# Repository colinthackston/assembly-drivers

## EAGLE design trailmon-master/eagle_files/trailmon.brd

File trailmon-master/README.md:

# trailmon
Hardware targeted at the trail counter project

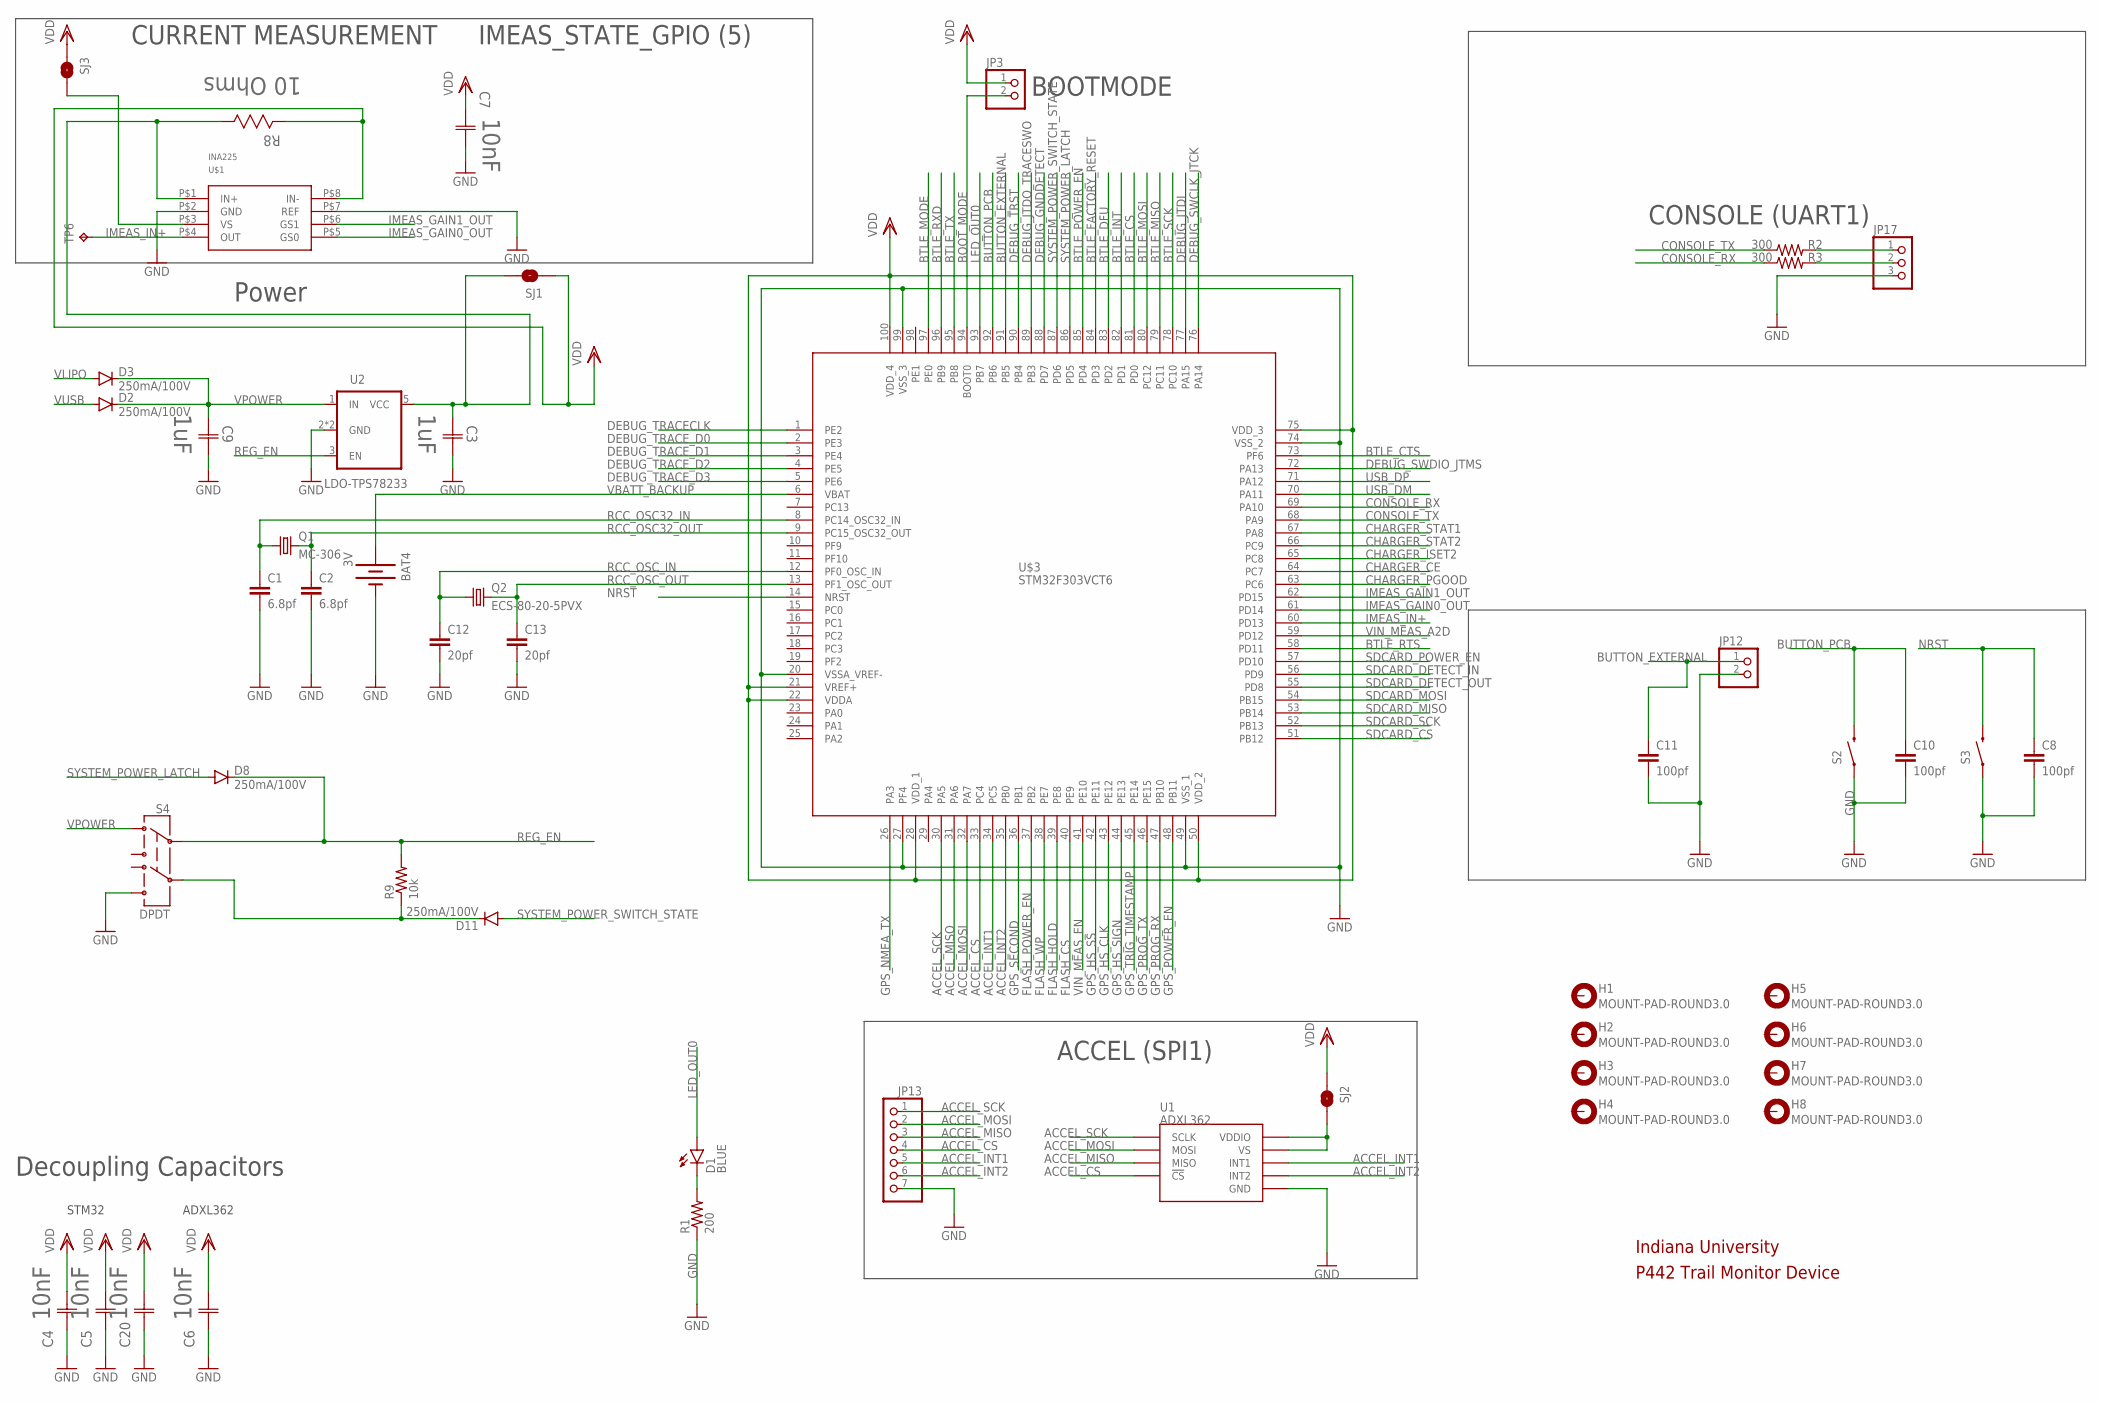
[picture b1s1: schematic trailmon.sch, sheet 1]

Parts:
BAT4: 3V; BATTCON_12MM
C1, C2: 6.8pf; 0603-CAP
C3, C9: 1uF; CAPC2013X110N
C4, C5, C6, C7, C20: 10nF; CAPC2013X88N
C8, C10, C11: 100pf; 0805
C12, C13: 20pf; 0603-CAP
D1: BLUE; LED-0603
D2, D3, D8, D11: 250mA/100V; SOD-323
H1, H2, H3, H4, H5, H6, H7, H8: MOUNT-PAD-ROUND3.0; 3,0-PAD
JP3, JP12: PINHD-1X2; 1X02
JP13: PINHD-1X7; 1X07
JP17: PINHD-1X3; 1X03
Q1: MC-306
Q2: ECS-80-20-5PVX; CSM-7X-DU
R1: 200; 0603-RES
R2, R3: 300; 0805
R8: 10 Ohms; RESC1608X60N
R9: 10k; 0603-RES
S2, S3: SWITCH-MOMENTARY-2SMD; TACTILE-SWITCH-SMD
S4: DPDT; AYZ0202
SJ1, SJ2, SJ3: JUMPER-PAD-2-NOYES_SILK; PAD-JUMPER-2-NO_YES_SILK
TP6: TPB1,27; B1,27
U1: ADXL362
U2: LDO-TPS78233; SOT23-5
U$1: INA225; MSOP-8
U$3: STM32F303VCT6; TQFP100

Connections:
ACCEL_CS: JP13.4, U1.P$8 (!CS), U$3.33 (PC4)
ACCEL_INT1: JP13.5, U1.P$11 (INT1), U$3.34 (PC5)
ACCEL_INT2: JP13.6, U1.P$9 (INT2), U$3.35 (PB0)
ACCEL_MISO: JP13.3, U1.P$7 (MISO), U$3.31 (PA6)
ACCEL_MOSI: JP13.2, U1.P$6 (MOSI), U$3.32 (PA7)
ACCEL_SCK: JP13.1, U1.P$4 (SCLK), U$3.30 (PA5)
BOOT_MODE: JP3.2, U$3.94 (BOOT0)
BTLE_CS: U$3.81 (PD0); also elsewhere on the board
BTLE_CTS: U$3.73 (PF6); also elsewhere on the board
BTLE_DFU: U$3.83 (PD2); also elsewhere on the board
BTLE_FACTORY_RESET: U$3.84 (PD3); also elsewhere on the board
BTLE_INT: U$3.82 (PD1); also elsewhere on the board
BTLE_MISO: U$3.79 (PC11); also elsewhere on the board
BTLE_MODE: U$3.97 (PE0); also elsewhere on the board
BTLE_MOSI: U$3.80 (PC12); also elsewhere on the board
BTLE_POWER_EN: U$3.85 (PD4); also elsewhere on the board
BTLE_RTS: U$3.58 (PD11); also elsewhere on the board
BTLE_RXD: U$3.96 (PB9); also elsewhere on the board
BTLE_SCK: U$3.78 (PC10); also elsewhere on the board
BTLE_TX: U$3.95 (PB8); also elsewhere on the board
BUTTON_EXTERNAL: C11.1, JP12.1, U$3.91 (PB5)
BUTTON_PCB: C10.1, S2.3 (2), U$3.92 (PB6)
CHARGER_CE: U$3.64 (PC7); also elsewhere on the board
CHARGER_ISET2: U$3.65 (PC8); also elsewhere on the board
CHARGER_PGOOD: U$3.63 (PC6); also elsewhere on the board
CHARGER_STAT1: U$3.67 (PA8); also elsewhere on the board
CHARGER_STAT2: U$3.66 (PC9); also elsewhere on the board
CONSOLE_RX: R3.1, U$3.69 (PA10)
CONSOLE_TX: R2.1, U$3.68 (PA9)
DEBUG_GNDDETECT: U$3.88 (PD7)
DEBUG_JTDI: U$3.77 (PA15); also elsewhere on the board
DEBUG_JTDO_TRACESWO: U$3.89 (PB3); also elsewhere on the board
DEBUG_SWCLK_JTCK: U$3.76 (PA14); also elsewhere on the board
DEBUG_SWDIO_JTMS: U$3.72 (PA13); also elsewhere on the board
DEBUG_TRACECLK: U$3.1 (PE2); also elsewhere on the board
DEBUG_TRACE_D0: U$3.2 (PE3); also elsewhere on the board
DEBUG_TRACE_D1: U$3.3 (PE4); also elsewhere on the board
DEBUG_TRACE_D2: U$3.4 (PE5); also elsewhere on the board
DEBUG_TRACE_D3: U$3.5 (PE6); also elsewhere on the board
DEBUG_TRST: U$3.90 (PB4); also elsewhere on the board
FLASH_CS: U$3.40 (PE9); also elsewhere on the board
FLASH_HOLD: U$3.39 (PE8); also elsewhere on the board
FLASH_POWER_EN: U$3.37 (PB2); also elsewhere on the board
FLASH_WP: U$3.38 (PE7); also elsewhere on the board
GND: BAT4.GND (-), C1.2, C2.2, C3.2 (C2), C4.1 (C1), C5.1 (C1), C6.1 (C1), C7.2 (C2), C8.2, C9.2 (C2), C10.2, C11.2, C12.2, C13.2, C20.1 (C1), JP12.2, JP13.7, JP17.3, R1.1, S2.1, S3.1, S4.6, U1.P$12 (GND), U1.P$13 (GND), U1.P$16 (GND), U2.2 (GND), U2.4 (GND), U$1.P$2 (GND), U$1.P$7 (REF), U$3.20 (VSSA_VREF-), U$3.27 (PF4), U$3.49 (VSS_1), U$3.74 (VSS_2), U$3.99 (VSS_3); also elsewhere on the board
GPS_HS_CLK: U$3.43 (PE12); also elsewhere on the board
GPS_HS_SIGN: U$3.44 (PE13); also elsewhere on the board
GPS_HS_SS: U$3.42 (PE11); also elsewhere on the board
GPS_NMEA_TX: U$3.26 (PA3); also elsewhere on the board
GPS_POWER_EN: U$3.48 (PB11); also elsewhere on the board
GPS_PROG_RX: U$3.47 (PB10); also elsewhere on the board
GPS_PROG_TX: U$3.46 (PE15); also elsewhere on the board
GPS_SECOND: U$3.36 (PB1); also elsewhere on the board
GPS_TRIG_TIMESTAMP: U$3.45 (PE14); also elsewhere on the board
IMEAS_GAIN0_OUT: U$1.P$5 (GS0), U$3.61 (PD14)
IMEAS_GAIN1_OUT: U$1.P$6 (GS1), U$3.62 (PD15)
IMEAS_IN+: TP6.TP, U$1.P$4 (OUT), U$3.60 (PD13)
LED_OUT0: D1.A, U$3.93 (PB7)
unnamed: D1.C, R1.2
unnamed: D11.C, R9.1, S4.5
unnamed: JP17.1, R2.2
unnamed: JP17.2, R3.2
unnamed: SJ2.2, U1.P$1 (VDDIO), U1.P$14 (VS)
unnamed: SJ3.2, U$1.P$3 (VS)
NRST: C8.1, S3.3 (2), U$3.14 (NRST); also elsewhere on the board
RCC_OSC32_IN: C1.1, Q1.1, U$3.8 (PC14_OSC32_IN)
RCC_OSC32_OUT: C2.1, Q1.4 (2), U$3.9 (PC15_OSC32_OUT)
RCC_OSC_IN: C12.1, Q2.1, U$3.12 (PF0_OSC_IN)
RCC_OSC_OUT: C13.1, Q2.2, U$3.13 (PF1_OSC_OUT)
REG_EN: D8.C, R9.2, S4.2, U2.3 (EN)
SDCARD_CS: U$3.51 (PB12); also elsewhere on the board
SDCARD_DETECT_IN: U$3.56 (PD9); also elsewhere on the board
SDCARD_DETECT_OUT: U$3.55 (PD8); also elsewhere on the board
SDCARD_MISO: U$3.53 (PB14); also elsewhere on the board
SDCARD_MOSI: U$3.54 (PB15); also elsewhere on the board
SDCARD_POWER_EN: U$3.57 (PD10); also elsewhere on the board
SDCARD_SCK: U$3.52 (PB13); also elsewhere on the board
SYSTEM_POWER_LATCH: D8.A, U$3.86 (PD5)
SYSTEM_POWER_SWITCH_STATE: D11.A, U$3.87 (PD6)
USB_DM: U$3.70 (PA11); also elsewhere on the board
USB_DP: U$3.71 (PA12); also elsewhere on the board
VBATT_BACKUP: BAT4.PWR@1 (+), U$3.6 (VBAT)
VCC: C3.1 (C1), R8.1, SJ1.2, U2.5 (VCC), U$1.P$1 (IN+)
VDD: C4.2 (C2), C5.2 (C2), C6.2 (C2), C7.1 (C1), C20.2 (C2), JP3.1, R8.2, SJ1.1, SJ2.1, SJ3.1, U$1.P$8 (IN-), U$3.21 (VREF+), U$3.22 (VDDA), U$3.28 (VDD_1), U$3.50 (VDD_2), U$3.75 (VDD_3), U$3.100 (VDD_4); also elsewhere on the board
VIN_MEAS_A2D: U$3.59 (PD12); also elsewhere on the board
VIN_MEAS_EN: U$3.41 (PE10); also elsewhere on the board
VLIPO: D3.A; also elsewhere on the board
VPOWER: C9.1 (C1), D2.C, D3.C, S4.1, U2.1 (IN)
VUSB: D2.A; also elsewhere on the board

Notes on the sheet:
Indiana University
Decoupling Capacitors
STM32
ADXL362
Power
ACCEL (SPI1)
BOOTMODE
CONSOLE (UART1)
CURRENT MEASUREMENT
P442 Trail Monitor Device
IMEAS_STATE_GPIO (5)

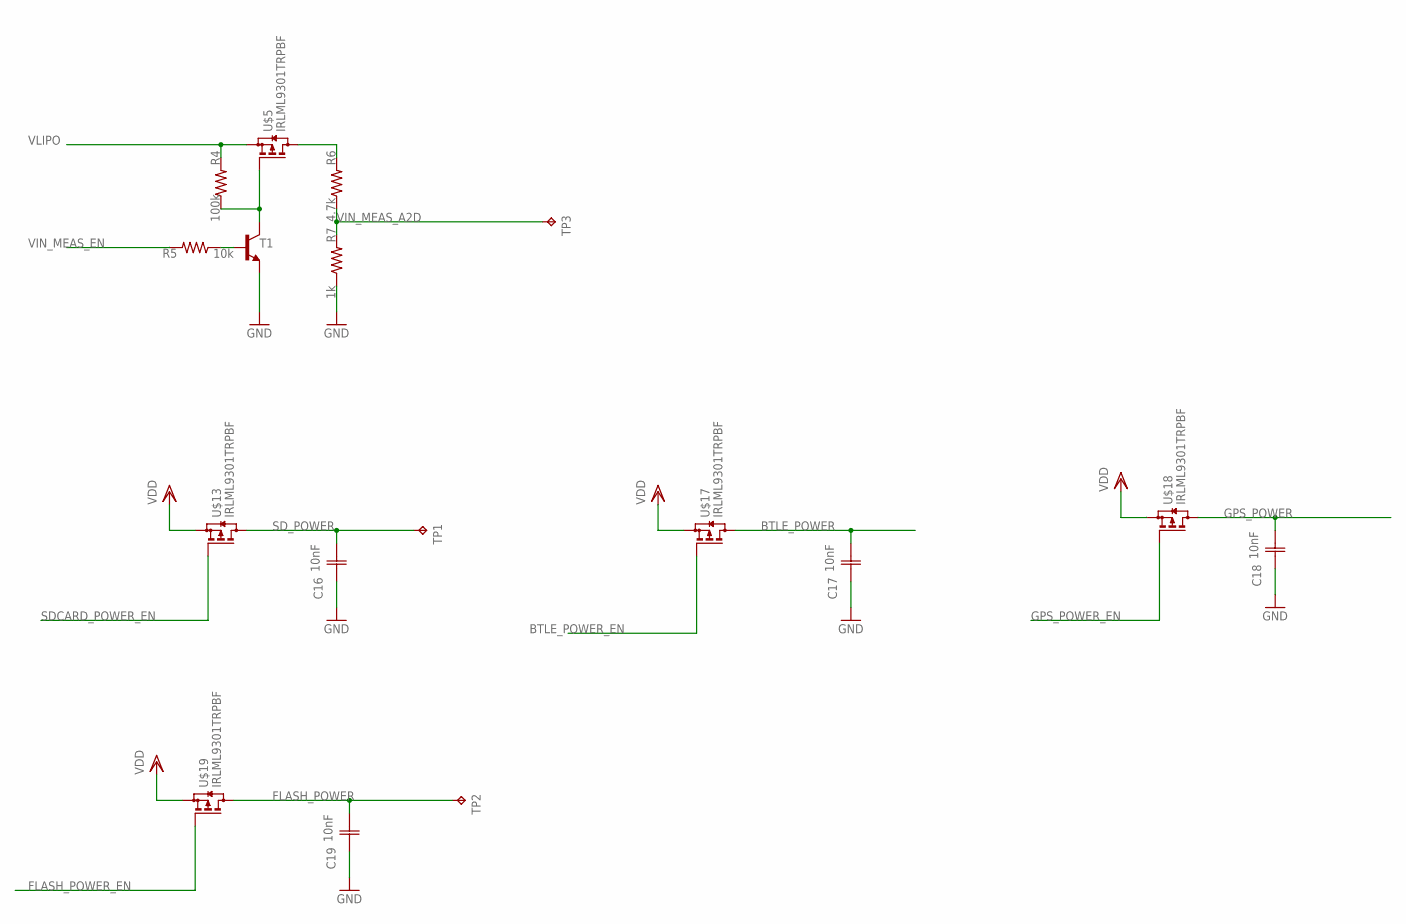
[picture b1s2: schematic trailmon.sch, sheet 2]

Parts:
C16, C17, C18, C19: 10nF; CAPC2013X88N
R4: 100k; 0805
R5: 10k; 0805
R6: 4.7k; 0805
R7: 1k; 0805
T1: BC847; SOT23
TP1, TP2, TP3: TPB1,27; B1,27
U$5, U$13, U$17, U$18, U$19: IRLML9301TRPBF; SOT23

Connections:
BTLE_POWER: C17.2 (C2), U$17.3 (D); also elsewhere on the board
BTLE_POWER_EN: U$17.1 (G); also elsewhere on the board
FLASH_POWER: C19.2 (C2), TP2.TP, U$19.3 (D); also elsewhere on the board
FLASH_POWER_EN: U$19.1 (G); also elsewhere on the board
GND: C16.1 (C1), C17.1 (C1), C18.1 (C1), C19.1 (C1), R7.1, T1.2 (E); also elsewhere on the board
GPS_POWER: C18.2 (C2), U$18.3 (D); also elsewhere on the board
GPS_POWER_EN: U$18.1 (G); also elsewhere on the board
unnamed: R5.1, T1.1 (B)
unnamed: R4.1, T1.3 (C), U$5.1 (G)
unnamed: R6.2, U$5.3 (D)
SDCARD_POWER_EN: U$13.1 (G); also elsewhere on the board
SD_POWER: C16.2 (C2), TP1.TP, U$13.3 (D); also elsewhere on the board
VDD: U$13.2 (S), U$17.2 (S), U$18.2 (S), U$19.2 (S); also elsewhere on the board
VIN_MEAS_A2D: R6.1, R7.2, TP3.TP; also elsewhere on the board
VIN_MEAS_EN: R5.2; also elsewhere on the board
VLIPO: R4.2, U$5.2 (S); also elsewhere on the board

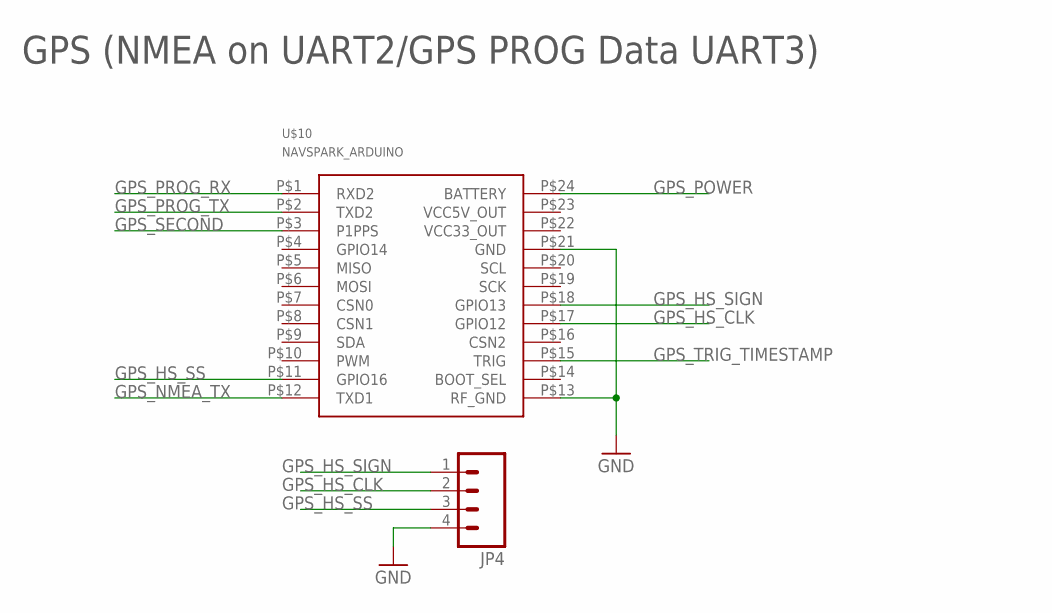
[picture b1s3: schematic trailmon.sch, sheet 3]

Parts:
JP4: M04PTH; 1X04
U$10: NAVSPARK_ARDUINO

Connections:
GND: JP4.4, U$10.P$13 (RF_GND), U$10.P$21 (GND); also elsewhere on the board
GPS_HS_CLK: JP4.2, U$10.P$17 (GPIO12); also elsewhere on the board
GPS_HS_SIGN: JP4.1, U$10.P$18 (GPIO13); also elsewhere on the board
GPS_HS_SS: JP4.3, U$10.P$11 (GPIO16); also elsewhere on the board
GPS_NMEA_TX: U$10.P$12 (TXD1); also elsewhere on the board
GPS_POWER: U$10.P$24 (BATTERY); also elsewhere on the board
GPS_PROG_RX: U$10.P$1 (RXD2); also elsewhere on the board
GPS_PROG_TX: U$10.P$2 (TXD2); also elsewhere on the board
GPS_SECOND: U$10.P$3 (P1PPS); also elsewhere on the board
GPS_TRIG_TIMESTAMP: U$10.P$15 (TRIG); also elsewhere on the board

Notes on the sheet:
GPS (NMEA on UART2/GPS PROG Data UART3)

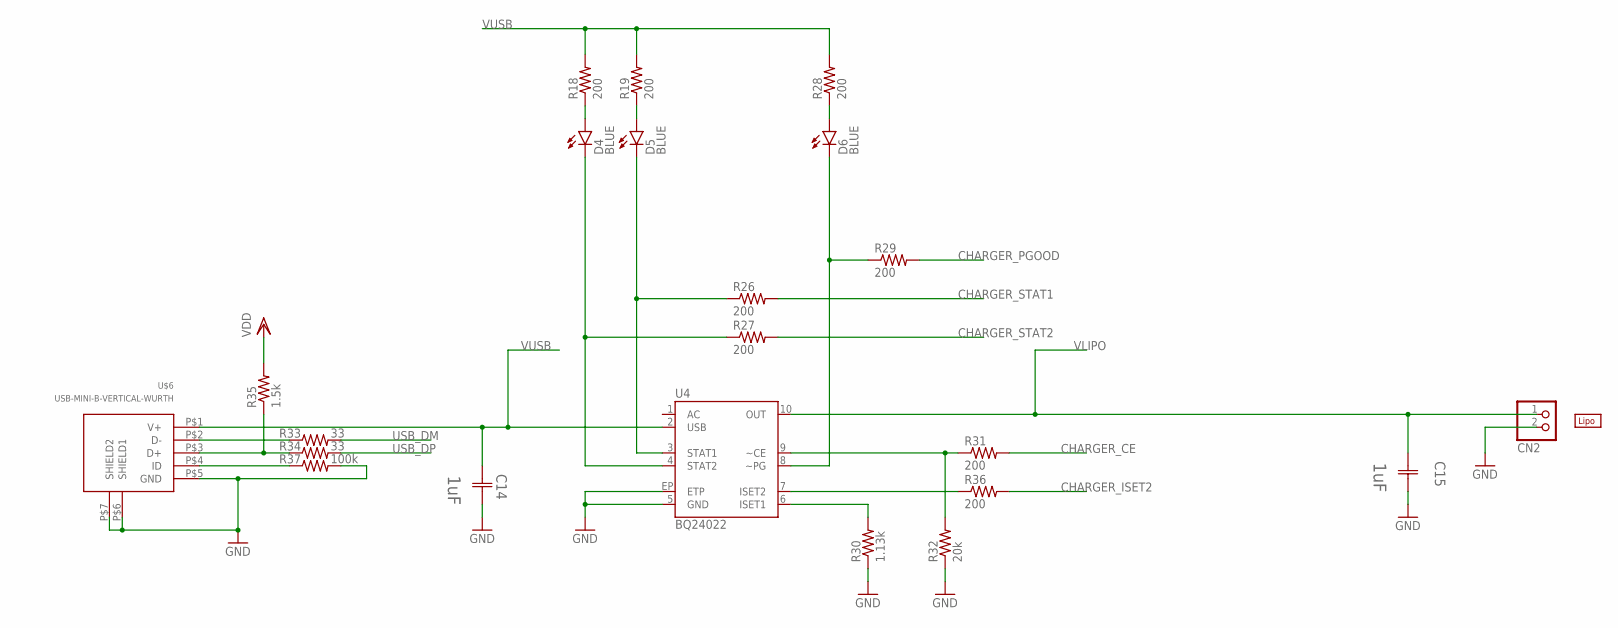
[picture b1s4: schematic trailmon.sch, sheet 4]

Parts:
C14, C15: 1uF; CAPC2013X110N
CN2: JST_2PIN-THM; JST-PH-2-THM
D4, D5, D6: BLUE; LED-0603
R18, R19, R26, R27, R28, R29, R31, R36: 200; 0603-RES
R30: 1.13k; 0603-RES
R32: 20k; 0603-RES
R33, R34: 33; 0603-RES
R35: 1.5k; 0603-RES
R37: 100k; 0603-RES
U4: BQ24022; DRC-10
U$6: USB-MINI-B-VERTICAL-WURTH; MINI-B-VERTICAL-WURTH
U$16: LIPO-OUTLINE1100; LIPO-1100

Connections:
CHARGER_CE: R31.2; also elsewhere on the board
CHARGER_ISET2: R36.2; also elsewhere on the board
CHARGER_PGOOD: R29.2; also elsewhere on the board
CHARGER_STAT1: R26.2; also elsewhere on the board
CHARGER_STAT2: R27.2; also elsewhere on the board
GND: C14.2 (C2), C15.2 (C2), CN2.2 (1), R30.1, R32.1, R37.2, U4.5 (GND), U4.EP (ETP), U$6.P$5 (GND), U$6.P$6 (SHIELD1), U$6.P$7 (SHIELD2); also elsewhere on the board
unnamed: D4.C, R27.1, U4.4 (STAT2)
unnamed: R33.1, U$6.P$2 (D-)
unnamed: D4.A, R18.1
unnamed: D5.C, R26.1, U4.3 (STAT1)
unnamed: D5.A, R19.1
unnamed: D6.A, R28.1
unnamed: D6.C, R29.1, U4.8 (~PG)
unnamed: R30.2, U4.6 (ISET1)
unnamed: R31.1, R32.2, U4.9 (~CE)
unnamed: R34.1, R35.1, U$6.P$3 (D+)
unnamed: R36.1, U4.7 (ISET2)
unnamed: R37.1, U$6.P$4 (ID)
USB_DM: R33.2; also elsewhere on the board
USB_DP: R34.2; also elsewhere on the board
VDD: R35.2; also elsewhere on the board
VLIPO: C15.1 (C1), CN2.1 (2), U4.10 (OUT); also elsewhere on the board
VUSB: C14.1 (C1), R18.2, R19.2, R28.2, U4.2 (USB), U$6.P$1 (V+); also elsewhere on the board

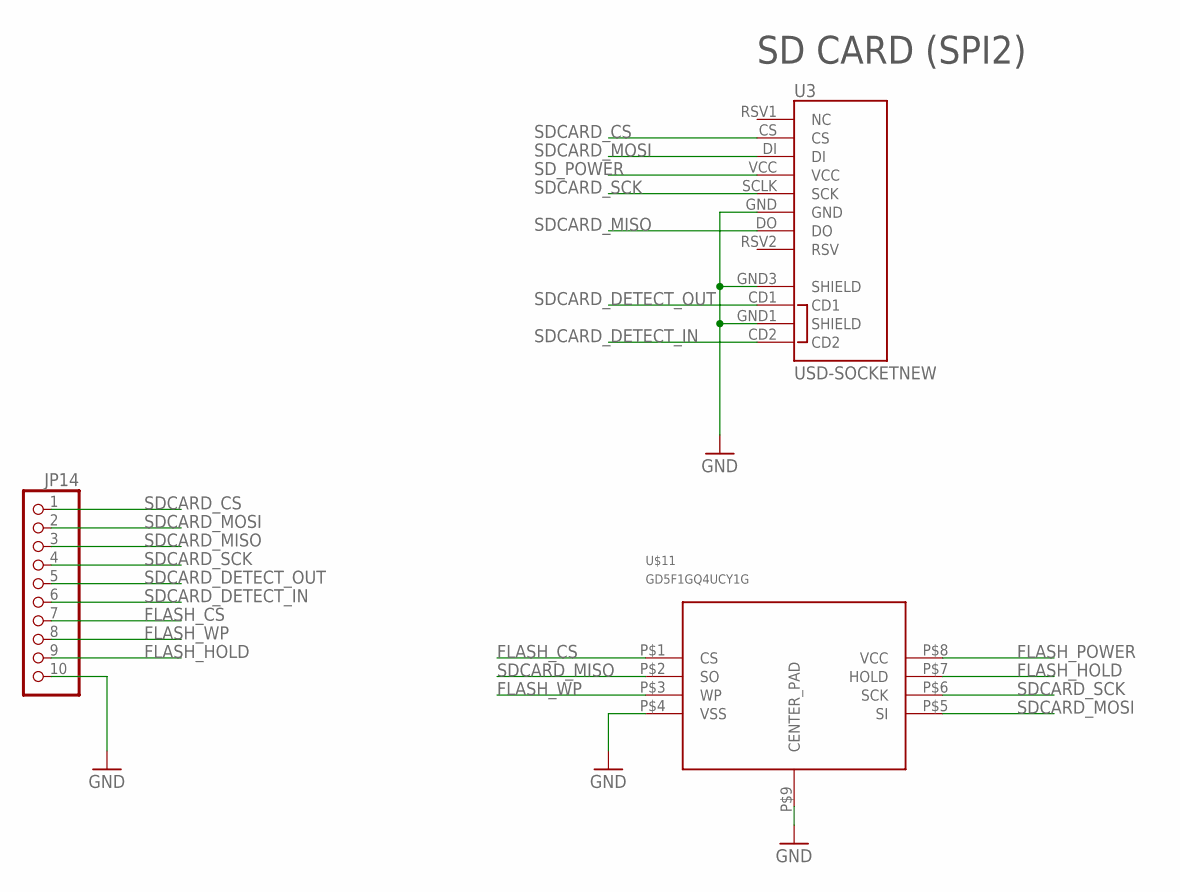
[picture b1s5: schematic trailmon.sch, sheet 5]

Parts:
JP14: PINHD-1X10; 1X10
U3: USD-SOCKETNEW; MICRO-SD-SOCKET-PP
U$11: GD5F1GQ4UCY1G; WSON-8

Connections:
FLASH_CS: JP14.7, U$11.P$1 (CS); also elsewhere on the board
FLASH_HOLD: JP14.9, U$11.P$7 (HOLD); also elsewhere on the board
FLASH_POWER: U$11.P$8 (VCC); also elsewhere on the board
FLASH_WP: JP14.8, U$11.P$3 (WP); also elsewhere on the board
GND: JP14.10, U3.GND, U3.GND1 (SHIELD), U3.GND3 (SHIELD), U$11.P$4 (VSS), U$11.P$9 (CENTER_PAD); also elsewhere on the board
SDCARD_CS: JP14.1, U3.CS; also elsewhere on the board
SDCARD_DETECT_IN: JP14.6, U3.CD2; also elsewhere on the board
SDCARD_DETECT_OUT: JP14.5, U3.CD1; also elsewhere on the board
SDCARD_MISO: JP14.3, U3.DO, U$11.P$2 (SO); also elsewhere on the board
SDCARD_MOSI: JP14.2, U3.DI, U$11.P$5 (SI); also elsewhere on the board
SDCARD_SCK: JP14.4, U3.SCLK (SCK), U$11.P$6 (SCK); also elsewhere on the board
SD_POWER: U3.VCC; also elsewhere on the board

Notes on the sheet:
SD CARD (SPI2)

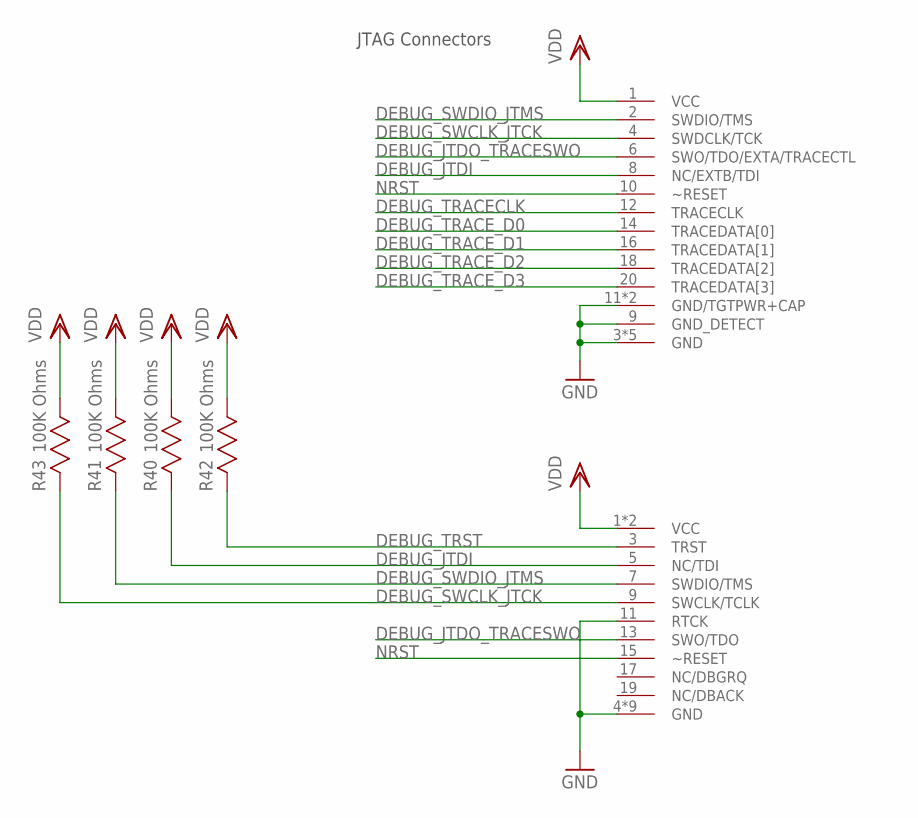
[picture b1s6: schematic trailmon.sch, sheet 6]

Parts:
R40, R41, R42, R43: 100K Ohms; RESC1005X40N
U$2: 2X10_0.05"_CORTEX_DEBUG_WITH_ETMSMD_UNSHROUDED; 2X10_0.05"_SMD_NS
U$12: TRADITIONALJTAG/SWDTH_SHROUDED; 2X10_0.1"_TH_SH

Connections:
DEBUG_JTDI: R40.2, U$2.8 (NC/EXTB/TDI), U$12.5 (NC/TDI); also elsewhere on the board
DEBUG_JTDO_TRACESWO: U$2.6 (SWO/TDO/EXTA/TRACECTL), U$12.13 (SWO/TDO); also elsewhere on the board
DEBUG_SWCLK_JTCK: R43.2, U$2.4 (SWDCLK/TCK), U$12.9 (SWCLK/TCLK); also elsewhere on the board
DEBUG_SWDIO_JTMS: R41.2, U$2.2 (SWDIO/TMS), U$12.7 (SWDIO/TMS); also elsewhere on the board
DEBUG_TRACECLK: U$2.12 (TRACECLK); also elsewhere on the board
DEBUG_TRACE_D0: U$2.14 (TRACEDATA[0]); also elsewhere on the board
DEBUG_TRACE_D1: U$2.16 (TRACEDATA[1]); also elsewhere on the board
DEBUG_TRACE_D2: U$2.18 (TRACEDATA[2]); also elsewhere on the board
DEBUG_TRACE_D3: U$2.20 (TRACEDATA[3]); also elsewhere on the board
DEBUG_TRST: R42.2, U$12.3 (TRST); also elsewhere on the board
GND: U$2.3 (GND), U$2.5 (GND), U$2.9 (GND_DETECT), U$2.11 (GND/TGTPWR+CAP), U$2.13 (GND/TGTPWR+CAP), U$2.15 (GND), U$2.17 (GND), U$2.19 (GND), U$12.4 (GND), U$12.6 (GND), U$12.8 (GND), U$12.10 (GND), U$12.11 (RTCK), U$12.12 (GND), U$12.14 (GND), U$12.16 (GND), U$12.18 (GND), U$12.20 (GND); also elsewhere on the board
NRST: U$2.10 (~RESET), U$12.15 (~RESET); also elsewhere on the board
VDD: R40.1, R41.1, R42.1, R43.1, U$2.1 (VCC), U$12.1 (VCC), U$12.2 (VCC); also elsewhere on the board

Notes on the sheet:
JTAG Connectors

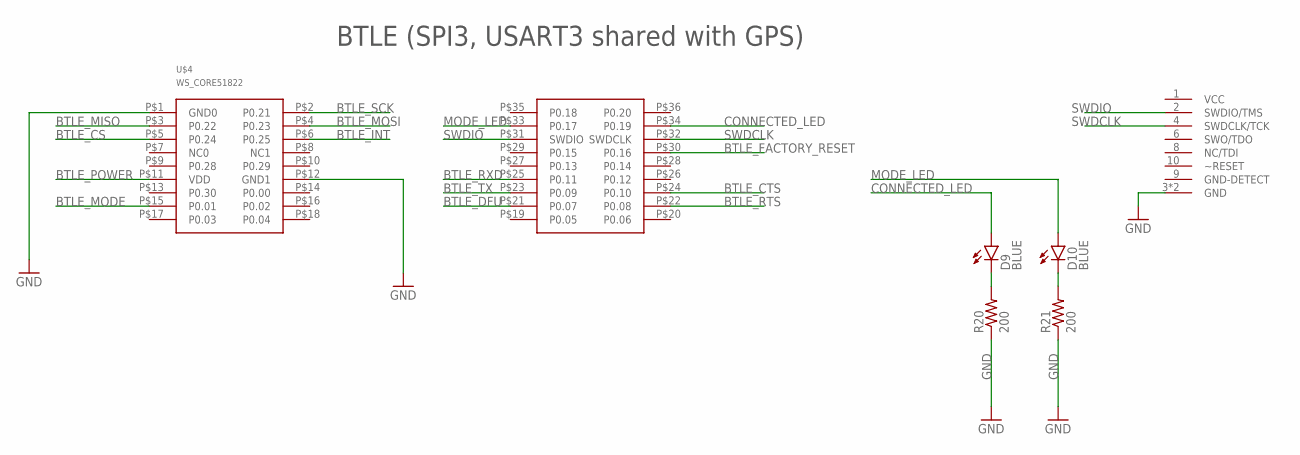
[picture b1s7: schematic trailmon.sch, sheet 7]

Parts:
D9, D10: BLUE; LED-0603
R20, R21: 200; 0603-RES
U$4: WS_CORE51822
U$15: 2X5_0.05"_CORTEX_DEBUGTH_NOKEY_UNSHROUDED; 2X5_0.05"_TH_NS

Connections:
BTLE_CS: U$4.P$5 (P0.24); also elsewhere on the board
BTLE_CTS: U$4.P$24 (P0.10); also elsewhere on the board
BTLE_DFU: U$4.P$21 (P0.07); also elsewhere on the board
BTLE_FACTORY_RESET: U$4.P$30 (P0.16); also elsewhere on the board
BTLE_INT: U$4.P$6 (P0.25); also elsewhere on the board
BTLE_MISO: U$4.P$3 (P0.22); also elsewhere on the board
BTLE_MODE: U$4.P$15 (P0.01); also elsewhere on the board
BTLE_MOSI: U$4.P$4 (P0.23); also elsewhere on the board
BTLE_POWER: U$4.P$11 (VDD); also elsewhere on the board
BTLE_RTS: U$4.P$22 (P0.08); also elsewhere on the board
BTLE_RXD: U$4.P$25 (P0.11); also elsewhere on the board
BTLE_SCK: U$4.P$2 (P0.21); also elsewhere on the board
BTLE_TX: U$4.P$23 (P0.09); also elsewhere on the board
CONNECTED_LED: D9.A, U$4.P$34 (P0.19)
GND: R20.1, R21.1, U$4.P$1 (GND0), U$4.P$12 (GND1), U$15.3 (GND), U$15.5 (GND); also elsewhere on the board
MODE_LED: D10.A, U$4.P$33 (P0.17)
unnamed: D9.C, R20.2
unnamed: D10.C, R21.2
SWDCLK: U$4.P$32 (SWDCLK), U$15.4 (SWDCLK/TCK)
SWDIO: U$4.P$31 (SWDIO), U$15.2 (SWDIO/TMS)

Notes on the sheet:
BTLE (SPI3, USART3 shared with GPS)

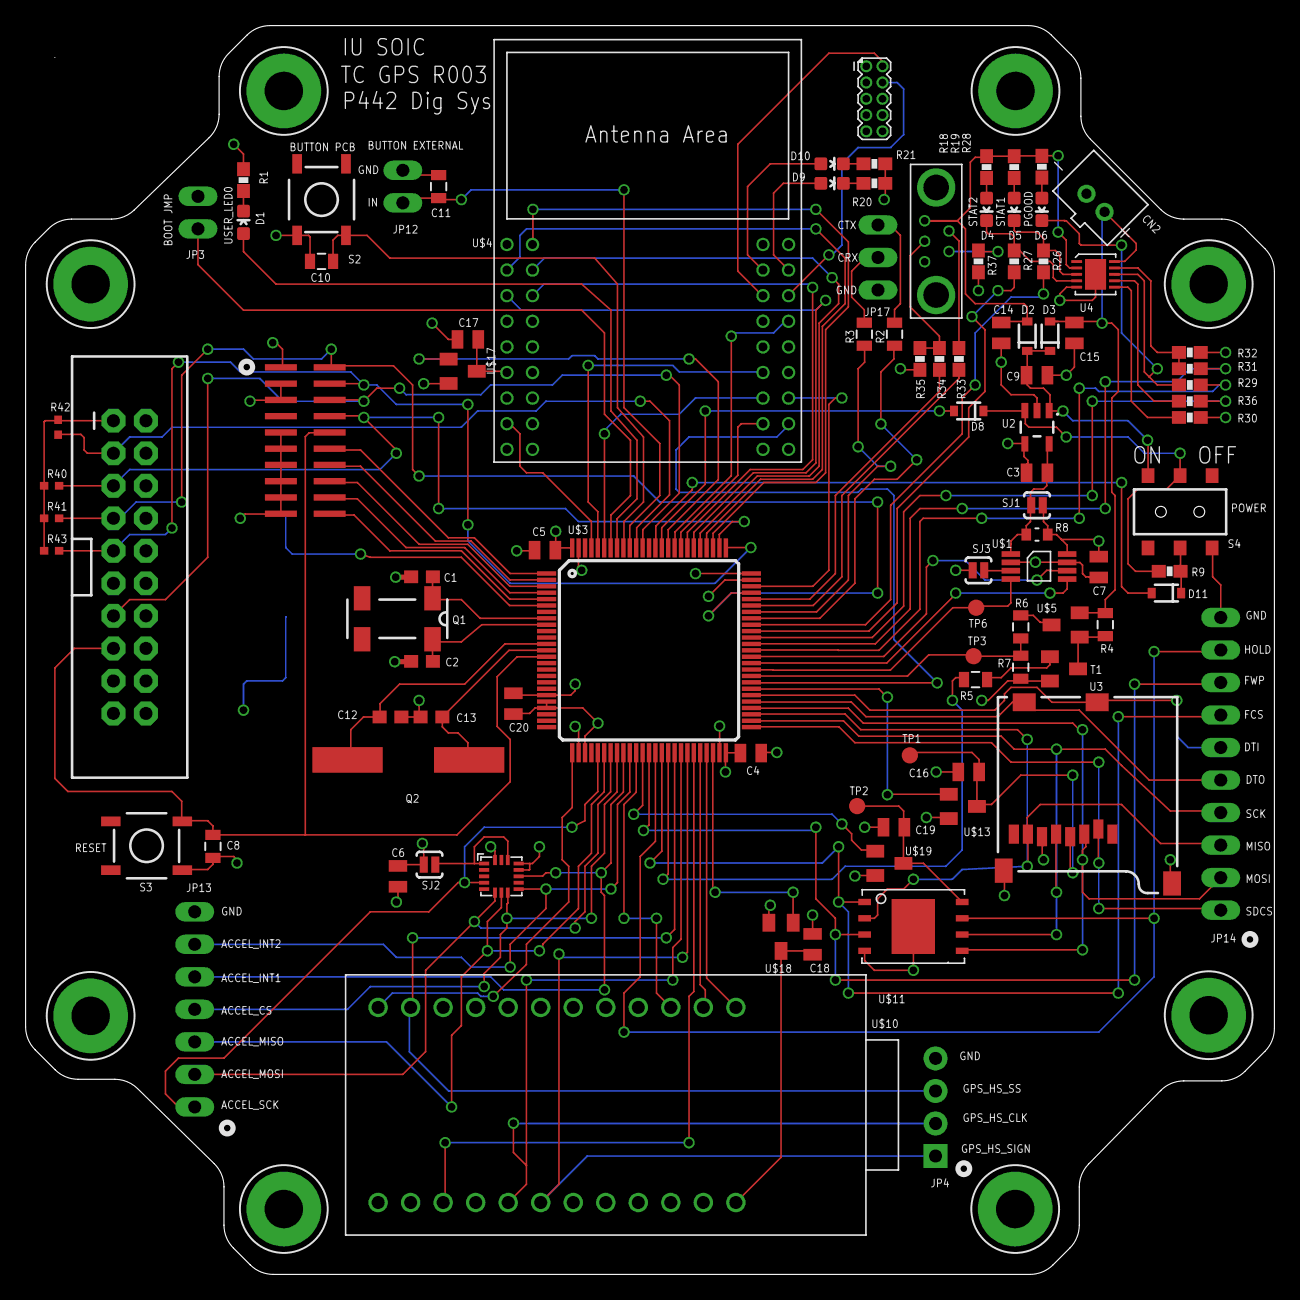
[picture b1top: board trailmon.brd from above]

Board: 4 copper layers, 97.5 x 97.5 mm, 107 parts (1 on the bottom side), 113 nets.

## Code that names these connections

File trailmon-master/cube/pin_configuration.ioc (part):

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Mcu.Name=STM32F303V(D-E)Tx
Mcu.Package=LQFP100
Mcu.UserName=STM32F303VETx
PA10.GPIOParameters=GPIO_Label
PA10.GPIO_Label=CONSOLE_RX
PA10.Mode=Asynchronous
PA10.Signal=USART1_RX
PA11.Mode=Device
PA11.Signal=USB_DM
PA12.Mode=Device
PA12.Signal=USB_DP
PA13.GPIOParameters=GPIO_Label
PA13.GPIO_Label=DEBUG_SWDIO_JTMS
PA13.Mode=Trace_Synchro_4bits_JTAG
PA13.Signal=SYS_JTMS-SWDIO
PA14.GPIOParameters=GPIO_Label
PA14.GPIO_Label=DEBUG_SWCLK_JTCK
PA14.Mode=Trace_Synchro_4bits_JTAG
PA14.Signal=SYS_JTCK-SWCLK
PA15.GPIOParameters=GPIO_Label
PA15.GPIO_Label=DEBUG_JTDI
PA15.Mode=Trace_Synchro_4bits_JTAG
PA15.Signal=SYS_JTDI
PA3.GPIOParameters=GPIO_Label
PA3.GPIO_Label=GPS_NMEA_TX
PA3.Signal=USART2_RX
PA5.GPIOParameters=GPIO_Label
PA5.GPIO_Label=ACCEL_SCK
PA5.Mode=Full_Duplex_Master
PA5.Signal=SPI1_SCK
PA6.GPIOParameters=GPIO_Label
PA6.GPIO_Label=ACCEL_MISO
PA6.Mode=Full_Duplex_Master
PA6.Signal=SPI1_MISO
PA7.GPIOParameters=GPIO_Label
PA7.GPIO_Label=ACCEL_MOSI
PA7.Mode=Full_Duplex_Master
PA7.Signal=SPI1_MOSI
PA8.GPIOParameters=GPIO_Label
PA8.GPIO_Label=CHARGER_STAT1
PA8.Signal=GPIO_Input
PA9.GPIOParameters=GPIO_Label
PA9.GPIO_Label=CONSOLE_TX
PA9.Mode=Asynchronous
PA9.Signal=USART1_TX
PB0.GPIOParameters=GPIO_Label
PB0.GPIO_Label=ACCEL_INT2
PB0.Signal=GPXTI0
PB1.GPIOParameters=GPIO_Label
PB1.GPIO_Label=GPS_SECOND
PB1.Signal=S_TIM3_CH4
PB10.GPIOParameters=GPIO_Label
PB10.GPIO_Label=GPS_PROG_RX
PB10.Mode=Asynchronous
PB10.Signal=USART3_TX
PB11.GPIOParameters=GPIO_Label
PB11.GPIO_Label=GPS_POWER_EN
PB11.Signal=GPIO_Output
PB12.GPIOParameters=GPIO_Label
PB12.GPIO_Label=SDCARD_CS
PB12.Signal=GPIO_Output
PB13.GPIOParameters=GPIO_Label
PB13.GPIO_Label=SDCARD_SCK
PB13.Mode=Full_Duplex_Master
PB13.Signal=SPI2_SCK
PB14.GPIOParameters=GPIO_Label
PB14.GPIO_Label=SDCARD_MISO
PB14.Mode=Full_Duplex_Master
PB14.Signal=SPI2_MISO
PB15.GPIOParameters=GPIO_Label
PB15.GPIO_Label=SDCARD_MOSI
PB15.Mode=Full_Duplex_Master
PB15.Signal=SPI2_MOSI
PB2.GPIOParameters=GPIO_Label
PB2.GPIO_Label=FLASH_POWER_EN
PB2.Signal=GPIO_Output
PB3.GPIOParameters=GPIO_Label
PB3.GPIO_Label=DEBUG_JTDO_TRACESWO
PB3.Mode=Trace_Synchro_4bits_JTAG
PB3.Signal=SYS_JTDO-TRACESWO
PB4.GPIOParameters=GPIO_Label
PB4.GPIO_Label=DEBUG_TRST
PB4.Signal=SYS_NJTRST
PB5.GPIOParameters=GPIO_Label
PB5.GPIO_Label=BUTTON_EXTERNAL
PB5.Signal=GPIO_Input
PB6.GPIOParameters=GPIO_Label
PB6.GPIO_Label=BUTTON_PCB
PB6.Signal=GPXTI6
PB7.GPIOParameters=GPIO_Label
PB7.GPIO_Label=LED_OUT
PB7.Signal=GPIO_Output
PB8.GPIOParameters=GPIO_Label
PB8.GPIO_Label=BTLE_TX
PB8.Signal=GPIO_Input
PB9.GPIOParameters=GPIO_Label
PB9.GPIO_Label=BTLE_RXD
PB9.Signal=GPIO_Output
PC10.GPIOParameters=GPIO_Label
PC10.GPIO_Label=BTLE_SCK
PC10.Mode=Full_Duplex_Master
PC10.Signal=SPI3_SCK
PC11.GPIOParameters=GPIO_Label
PC11.GPIO_Label=BTLE_MISO
PC11.Mode=Full_Duplex_Master
PC11.Signal=SPI3_MISO
PC12.GPIOParameters=GPIO_Label
PC12.GPIO_Label=BTLE_MOSI
PC12.Mode=Full_Duplex_Master
PC12.Signal=SPI3_MOSI
PC14-OSC32_IN.Mode=LSE-External-Oscillator
PC14-OSC32_IN.Signal=RCC_OSC32_IN
PC15-OSC32_OUT.Mode=LSE-External-Oscillator
PC15-OSC32_OUT.Signal=RCC_OSC32_OUT
PC4.GPIOParameters=GPIO_Label
PC4.GPIO_Label=ACCEL_CS
PC4.Signal=GPIO_Output
PC5.GPIOParameters=GPIO_Label
PC5.GPIO_Label=ACCEL_INT1
PC5.Signal=GPXTI5
PC6.GPIOParameters=GPIO_Label
PC6.GPIO_Label=CHARGER_PGOOD
PC6.Signal=GPIO_Input
PC7.GPIOParameters=GPIO_Label
PC7.GPIO_Label=CHARGER_CE
PC7.Signal=GPIO_Output
PC8.GPIOParameters=GPIO_Label
PC8.GPIO_Label=CHARGER_ISET2
PC8.Signal=GPIO_Output
PC9.GPIOParameters=GPIO_Label
PC9.GPIO_Label=CHARGER_STAT2
PC9.Signal=GPIO_Input
PD0.GPIOParameters=GPIO_Label
PD0.GPIO_Label=BTLE_CS
PD0.Signal=GPIO_Output
PD1.GPIOParameters=GPIO_Label
PD1.GPIO_Label=BTLE_INT
PD1.Signal=GPXTI1
PD10.GPIOParameters=GPIO_Label
PD10.GPIO_Label=SDCARD_POWER_EN
PD10.Signal=GPIO_Output
PD11.GPIOParameters=GPIO_Label
PD11.GPIO_Label=BTLE_RTS
PD11.Mode=CTS_RTS
PD11.Signal=USART3_CTS
PD12.GPIOParameters=GPIO_Label
PD12.GPIO_Label=VIN_MEAS_A2D
PD12.Signal=ADCx_IN9P
PD13.GPIOParameters=GPIO_Label
PD13.GPIO_Label=IMEAS_IN+
PD13.Signal=ADCx_IN10P
PD14.GPIOParameters=GPIO_Label
PD14.GPIO_Label=IMEAS_GAIN0_OUT
PD14.Signal=GPIO_Output
PD15.GPIOParameters=GPIO_Label
PD15.GPIO_Label=IMEAS_GAIN1_OUT
PD15.Signal=GPIO_Output
PD2.GPIOParameters=GPIO_Label
PD2.GPIO_Label=BTLE_DFU
PD2.Signal=GPIO_Output
PD3.GPIOParameters=GPIO_Label
PD3.GPIO_Label=BTLE_FACTORY_RESET
PD3.Signal=GPIO_Output
PD4.GPIOParameters=GPIO_Label
PD4.GPIO_Label=BTLE_POWER_EN
PD4.Signal=GPIO_Output
PD5.GPIOParameters=GPIO_Label
PD5.GPIO_Label=SYSTEM_POWER_LATCH
PD5.Signal=GPIO_Output
PD6.GPIOParameters=GPIO_Label
PD6.GPIO_Label=SYSTEM_POWER_SWITCH_STATE
PD6.Signal=GPIO_Output
PD7.GPIOParameters=GPIO_Label
PD7.GPIO_Label=DEBUG_GNDDETECT
PD7.Signal=GPIO_Input
PD8.GPIOParameters=GPIO_Label
PD8.GPIO_Label=SDCARD_DETECT_OUT
PD8.Signal=GPIO_Output
PD9.GPIOParameters=GPIO_Label
PD9.GPIO_Label=SDCARD_DETECT_IN
PD9.Signal=GPXTI9
PE0.GPIOParameters=GPIO_Label
PE0.GPIO_Label=BTLE_MODE
PE0.Signal=GPIO_Output
PE10.GPIOParameters=GPIO_Label
PE10.GPIO_Label=VIN_MEAS_EN
PE10.Signal=GPIO_Output
PE11.GPIOParameters=GPIO_Label
PE11.GPIO_Label=GPS_HS_SS
PE11.Mode=NSS_Signal_Hard_Input
PE11.Signal=SPI4_NSS
PE12.GPIOParameters=GPIO_Label
PE12.GPIO_Label=GPS_HS_CLK
PE12.Mode=Simplex_Bidirectional_Slave
PE12.Signal=SPI4_SCK
PE13.GPIOParameters=GPIO_Label
PE13.GPIO_Label=GPS_HS_SIGN
PE13.Mode=Simplex_Bidirectional_Slave
PE13.Signal=SPI4_MISO
PE14.GPIOParameters=GPIO_Label
PE14.GPIO_Label=GPS_TRIG_TIMESTAMP
PE14.Signal=GPIO_Output
PE15.GPIOParameters=GPIO_Label
PE15.GPIO_Label=GPS_PROG_TX
PE15.Mode=Asynchronous
PE15.Signal=USART3_RX
PE2.GPIOParameters=GPIO_Label
PE2.GPIO_Label=DEBUG_TRACECLK
PE2.Mode=Trace_Synchro_4bits_JTAG
PE2.Signal=SYS_TRACECK
PE3.GPIOParameters=GPIO_Label
PE3.GPIO_Label=DEBUG_TRACE_D0
PE3.Mode=Trace_Synchro_4bits_JTAG
PE3.Signal=SYS_TRACED0
PE4.GPIOParameters=GPIO_Label
PE4.GPIO_Label=DEBUG_TRACE_D1
PE4.Mode=Trace_Synchro_4bits_JTAG
PE4.Signal=SYS_TRACED1
PE5.GPIOParameters=GPIO_Label
PE5.GPIO_Label=DEBUG_TRACE_D2
PE5.Mode=Trace_Synchro_4bits_JTAG
PE5.Signal=SYS_TRACED2
PE6.GPIOParameters=GPIO_Label
PE6.GPIO_Label=DEBUG_TRACE_D3
PE6.Mode=Trace_Synchro_4bits_JTAG
PE6.Signal=SYS_TRACED3
PE7.GPIOParameters=GPIO_Label
PE7.GPIO_Label=FLASH_WP
PE7.Signal=GPIO_Output
PE8.GPIOParameters=GPIO_Label
PE8.GPIO_Label=FLASH_HOLD
PE8.Signal=GPIO_Output
PE9.GPIOParameters=GPIO_Label
PE9.GPIO_Label=FLASH_CS
PE9.Signal=GPIO_Output
PF0-OSC_IN.Mode=HSE-External-Oscillator
PF0-OSC_IN.Signal=RCC_OSC_IN
PF1-OSC_OUT.Mode=HSE-External-Oscillator
PF1-OSC_OUT.Signal=RCC_OSC_OUT
PF6.GPIOParameters=GPIO_Label
PF6.GPIO_Label=BTLE_CTS
PF6.Mode=CTS_RTS
PF6.Signal=USART3_RTS
RCC.HSE_VALUE=8000000
RCC.SYSCLKFreq_VALUE=72000000
RCC.SYSCLKSourceVirtual=RCC_SYSCLKSOURCE_PLLCLK

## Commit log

2018-08-19 examples
2018-08-19 more drivers

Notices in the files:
parts and their libraries:
SparkFun-Sensors: Licensing: Creative Commons ShareAlike 4.0 International - https://creativecommons.org/licenses/by-sa/4.0
